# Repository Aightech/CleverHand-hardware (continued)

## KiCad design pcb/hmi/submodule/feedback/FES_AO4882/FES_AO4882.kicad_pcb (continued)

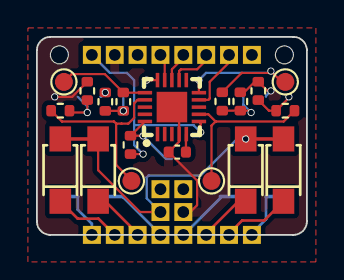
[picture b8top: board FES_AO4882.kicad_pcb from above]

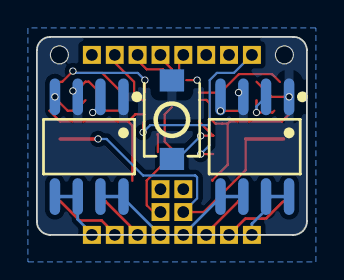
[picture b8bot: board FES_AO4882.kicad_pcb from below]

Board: 4 copper layers, 15.0 x 11.0 mm, 42 parts (3 on the bottom side), 26 nets.

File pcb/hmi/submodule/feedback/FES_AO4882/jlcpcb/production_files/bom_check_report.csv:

Status,RefDes,Qty,LCSC,BOM_Comment,LCSC_Package,LCSC_Describe,Matched,Issues,FallbackNote
OK,R2,1,C25744,10K,0402,-55℃~+155℃ 10kΩ 50V 62.5mW Thick Film Resistor ±1% ±100ppm/℃ 0402 Chip Resistor - Surface Mount ROHS,describe~substring,,
OK,"R1,R3,R6,R7",4,C11702,1k,0402,-55℃~+155℃ 1kΩ 50V 62.5mW Thick Film Resistor ±1% ±100ppm/℃ 0402 Chip Resistor - Surface Mount ROHS,describe~substring,,
OK,"R4,R5,R8,R9",4,C4109,2k,0402,-55℃~+155℃ 2kΩ 50V 62.5mW Thick Film Resistor ±1% ±100ppm/℃ 0402 Chip Resistor - Surface Mount ROHS,describe~substring,,
OK,C1,1,C23733,4.7uF,0402,10V 4.7uF X5R ±20% 0402 Multilayer Ceramic Capacitors MLCC - SMD/SMT ROHS,capacitance,,
FAIL,"Q1,Q2",2,C3040598,AO4882_C3040598,,-50℃~+150℃ 1.45nF 140pF 2 N-Channel 2.5V@250uA 21.6nC@10V 220pF@25V 25mΩ@4.5V 2W 40V 8A SOP-8 MOSFETs ROHS,,no clear feature match for generic part,
OK,"U1,U2,U3,U5",4,C5120757,DS12W-MS,,-65℃~+125℃ 1A 20V 500uA@20V 550mV@1A Independent SOD-123FL Diodes - General Purpose ROHS,model/brand,,
OK,U4,1,C493490,HC32L110C6UA-SFN20TR,,1.8V~5.5V 12bit 16 32KB 32MHz ARM Cortex-M0 FLASH WQFN-20-EP(3x3) Microcontrollers (MCU/MPU/SOC) ROHS,model/brand,,
OK,SW1,1,C455280,TS-1088R-02026,,"100,000 Cycles 12V 2.6N 2.93mm 2mm 3.9mm 50mA Black Round Button SMD(SMT) Tab SPST Surface Mount,Vertical Without Bracket SMD,4x3mm Tactile Switches ROHS",model/brand,,

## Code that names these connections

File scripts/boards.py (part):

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# ============ COM_MOD_PAK ============
def com_mod_pak():
    s=Sheet("COM_MOD_PAK","COM_MOD_PAK - v3 communication module B (HC32L110 + SLG46826)")
    s.text("HC32L110C6UA QFN-20 (CSP-16 rejected: inner balls not routable with JLC rules). v2 pinout kept: SDA P35, SCL P36, STOP_IN P31 (=SWCLK), STOP_OUT P02, LED P01. Freed ADD pins: P34/P33 = private I2C to the GreenPAK, P03/P15/P14/P32 = AUX4..7 (node-local), P23 user button.",20,20,1.8)
    s.part("U","00_lcsc","HC32L110C6UA-SFN20TR",90,100,{
        "1":"RESETB","2":"LED_DI","3":g("STOP_OUT"),"4":G,"5":"VCAP","6":P3,"7":g("AUX4"),"8":g("AUX5"),"9":g("AUX6"),"10":"BTN",
        "11":"NC","12":"NC","13":"NC","14":"SWDIO","15":g("STOP_IN"),"16":g("AUX7"),"17":"PAK_SDA","18":"PAK_SCL","19":g("SDA"),"20":g("SCL"),"21":G},lcsc=LC["HC32"])
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# ============ BUS_FPC ============
def bus_fpc():
    s=Sheet("BUS_FPC","BUS_FPC - passive bus board, two 18-way FPC (v2 cable pinout)")
    s.text("IN connector: pin k = v2 cable pin k. OUT connector is pin-reversed (pin k = cable pin 19-k). STOP: IN -> STOP_IN, OUT <- STOP_OUT.",20,20,1.8)
    nin=dict(CABLE); nin["13"]=g("STOP_IN")
    s.part("J","00_lcsc","FPC-05F-18PH20",60,110,nin,lcsc=LC["FPC"],value="FPC IN")
    nout={}
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    nid={str(k):CABLE[str(k)] for k in range(1,19) if k!=13}; nid["13"]="NC"
    s.part("J","Connector_Generic","Conn_02x09_Odd_Even",70,110,nid,value="IDC 2x9 1.27",footprint="Connector_PinHeader_1.27mm:PinHeader_2x09_P1.27mm_Vertical_SMD")
    s.part("J","00_lcsc","SM02B-SRSS-TB(LF)(SN)",150,110,{"1":g("STOP_IN"),"2":g("STOP_OUT"),"3":G,"4":G},lcsc=LC["SH"],value="STOP link")
    s.text("STOP link: pin1 = STOP_IN (from previous node), pin2 = STOP_OUT (to next node); crossed 2-wire cable",120,125,1.3)
    stack_field(s,250,110,"bus","3x10 stack field: rows A+B and AUX0..3 connected, row C local lines left open")
    tp(s,60,180,"VIN_TP")
    s.passive("C","100nF",140,180,P3,G)
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    usb_block(s,60,210)
    battery_block(s,200,210,"MIC")
    dac_block(s,60,270)
    stack_field(s,330,90,"ctrl","3x10 stack field, CTRL: drives row B (STOP_IN unused), SDA_L/SCL_L strapped to SDA/SCL, VIN = battery, AUX0..3 on ADC pins, AUX4..7 on GPIO")
    s.flag("VBUS",20,250); s.flag("+BATT",30,250); s.flag("GND",40,250); s.flag("+3.3V",50,250)
    return s
# ============ CTRL_ESP32S3 ============
def ctrl_esp():
    s=Sheet("CTRL_ESP32S3","CTRL_ESP32S3 - ESP32-S3FH4R2 controller node (chip-down)")
    s.text("ESP32-S3FH4R2 chip-down: 40 MHz crystal, TDK chip antenna with pi-match (values TBD at tuning), native USB on GPIO19/20. Mono node or chain head; SDA_L/SCL_L strapped.",20,20,1.8)
    s.part("U","00_lcsc","ESP32-S3FH4R2",80,110,{
        "2":P3,"3":P3,"20":P3,"46":P3,"55":P3,"56":P3,"29":P3,"57":G,"4":"CHIP_PU","5":"GPIO0","1":"LNA_IN","53":"XTAL_N","54":"XTAL_P","25":"D-","26":"D+","49":"U0TXD","50":"U0RXD",
        "17":g("SCLK"),"16":g("PICO"),"18":g("POCI"),"15":g("CSB"),"14":g("AUX7"),"9":g("A0"),"10":g("A1"),"11":g("A2"),"12":g("A3"),"13":g("A4"),"19":g("STOP_OUT"),
        "6":g("SDA"),"7":g("SCL"),"8":g("AUX4"),"23":g("AUX7"),"24":g("AUX5"),"27":g("AUX6"),"43":"LED_DI","38":"BTN","39":g("AUX0"),"40":g("AUX1"),"41":g("AUX2"),"42":g("CLK"),"44":"CHG_STAT","45":g("AUX3"),
        "21":"NC","22":"NC","28":"NC","30":"NC","31":"NC","32":"NC","33":"NC","34":"NC","35":"NC","36":"NC","37":"NC","47":"NC","48":"NC","51":"NC","52":"NC"},lcsc=LC["ESP"])
    s.passive("C","10uF",150,60,P3,G,size="0402"); s.passive("C","100nF",160,60,P3,G); s.passive("C","100nF",170,60,P3,G); s.passive("C","100nF",180,60,P3,G); s.passive("C","1uF",190,60,P3,G)
    s.text("CHIP_PU: 10k pull-up + 1uF (RC reset), reset button. GPIO0: 10k pull-up + boot button.",150,80,1.3)
    s.passive("R","10k",150,95,P3,"CHIP_PU"); s.passive("C","1uF",160,95,"CHIP_PU",G); button(s,175,95,"CHIP_PU",False)
    s.passive("R","10k",150,125,P3,"GPIO0"); button(s,175,125,"GPIO0",False); button(s,215,125,"BTN")
    s.part("Y","00_lcsc","40MHZ_3225_12PF_10PPM",150,160,{"1":"XTAL_P","3":"XTAL_N","2":G,"4":G},lcsc=LC["XTAL"],value="40MHz 12pF")
    s.passive("C","12pF",170,160,"XTAL_P",G); s.passive("C","12pF",180,160,"XTAL_N",G)
    s.text("RF: LNA_IN -> C -> L -> ANT with shunt C (pi-match, values TBD)",150,185,1.3)
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    usb_block(s,60,260)
    battery_block(s,200,260,"AP")
    dac_block(s,60,320)
    stack_field(s,330,90,"ctrl","3x10 stack field, CTRL: drives row B (STOP_IN unused), SDA_L/SCL_L strapped to SDA/SCL, VIN = battery, AUX0..3 / AUX4..7 on GPIO")
    s.flag("VBUS",20,250); s.flag("+BATT",30,250); s.flag("GND",40,250); s.flag("+3.3V",50,250)
    return s
# ============ VIB_DRV2625 ============
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    s.part("U","00_lcsc","DRV2625YFFR",80,90,{"C2":P3,"B3":G,"A2":"REG","C3":"OUT-","A3":"OUT+","B1":g("SDA_L"),"C1":g("SCL_L"),"A1":g("AUX7"),"B2":g("AUX6")},lcsc=LC["DRV"])
    s.passive("C","1uF",130,80,"REG",G); s.passive("C","1uF",140,80,P3,G); s.passive("C","10uF",150,80,P3,G,size="0402")
    s.part("J","00_lcsc","SM02B-SRSS-TB(LF)(SN)",80,140,{"1":"OUT+","2":"OUT-","3":G,"4":G},lcsc=LC["SH"],value="MOTOR")
    stack_field(s,250,110,{"GND":G,"3V3":P3,"SDA_L":g("SDA_L"),"SCL_L":g("SCL_L"),"AUX6":g("AUX6"),"AUX7":g("AUX7")},"3x10 stack field, H-i2c: populate row A power pins, C1/C2 (local I2C), C7/C8 (AUX6/AUX7); other positions unpopulated")
    s.flag("+3.3V",20,200); s.flag("GND",30,200)
    return s

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
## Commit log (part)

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2021-08-24 v7-panel
    smd0201
2021-08-24 panelized
2021-08-29 jst sh conn
2021-08-29 dim changed to be panalized 3x4
2021-08-30 add rdy and sync
2021-09-24 placement
2021-09-24 gnd-vdd common
2021-09-24 finished
2021-09-24 pics
2021-09-25 panelization
2021-09-25 component val + minor debug
2021-09-26 Create clvHd.s##
2021-09-26 3d rendering
2021-09-26 update colors + text
2021-09-27 correction led
2021-09-27 redesign
2021-10-28 Xtal fixed + logo
2021-10-29 animation
2021-11-08 added master FES EMG folders
2021-11-26 almost fully routed
2021-11-27 ready for prod
2021-11-30 master update
2021-11-30 refactor git
2021-12-14 shrinken
2021-12-16 dir indication + lvl3 gnd plane
2022-01-23 double gate nand
2022-01-27 socket design
2022-02-06 long board
2022-04-12 global setup
2022-04-12 partial routing
2022-04-12 almost completely routed
2022-04-12 fully routed + text
2022-04-12 bottom stop correction + bottom text
2022-06-26 visual mod
2022-07-01 nand new package
    changed the json package for a vssop package to make is easier to solder. updated README, docs and CAM
2022-07-02 panelization + datasheet
2022-07-06 added stl model
2022-07-06 license and co
2022-07-06 added some pics
2022-07-15 neopixel
2022-07-16 fixed position c4-r1
2022-07-31 fixed g00 pinout
2022-10-26 v3.0 on kicad
2022-10-28 finished v3
2022-10-31 fixed some panel bug for jlcpcb
2022-11-01 v3.1 fixed solder and paste mask and some via pos
2022-12-30 cleanup directory
2023-02-22 new module with hc32l110 and some extension board
2023-05-29 lot of modification, preparing a refactor + some rendering
2023-09-08 updated bridge
2023-09-13 updated bridge board
2023-09-14 cleanup
2023-11-15 new version logicGate+hc32l to mitigate CS speed while keeping new features
2023-11-28 new modules EMGDAQ and COMMOD
2023-11-30 reshaped the modules boards sizes
2023-11-30 blender module assembly
2023-12-05 some cleaning + edge plating dry electrode
2023-12-05 some rendring
2023-12-07 finished rooting emgdaq + schematic commod
2023-12-30 lot of updates on ads93,flex,commod,pad
2024-01-02 finished ads93,commod,drypad,flexpad,jackconn,imubno + plot and render
2024-03-29 INA331 IMUICM
2024-03-29 jack, dry electrode
2024-03-30 refactor and fixing most of the modules
2024-03-30 new dry flex
2024-03-30 cleaned all modules + production files
2024-03-31 lot of rendering and documentaion
2024-04-01 fixed INA331 wrong package and add ext ref
2024-04-01 regenerated production files for INA331
2024-04-01 cleaned kicad folder
2024-04-01 renamed stl files
2024-04-17 renamed SPI buses
2024-06-24 fixed COM_MOD grounding issues
2024-07-02 Rename pinout2.png to initialisation/pinout2.png
2024-07-18 added progress state of the submodules
2024-07-28 minor update: added pins to access i2c pins of the com bus
2024-07-28 major update: fixed inversion of i2c lines + added pull up resistors + rotated 180deg fpc conector
2024-07-29 fixed ref number of FPC connectors and added ref numbers of resitors
2024-08-17 modified pins to expose in6 and gnd for potential filtering
2024-08-17 increase size of the board to make it easier to screw
2024-08-17 new dry electectrodes for ads1295 module
2024-08-17 pannel for new dry electrodes
2024-08-25 v3.2 fixed issue between GND and GNDA
2024-08-26 update production files of shield controller teensy
2024-09-02 mono controller, to have module working on their own and comunicate via wifi
2024-09-02 finished mono moudule, should be ready for manufacture
2024-09-02 fixed pico controller shield to match v3 modules
2024-09-02 minor fix on teensy shield
2024-09-03 fixed MONOCOM ERC and DRC: via size, missing pins
2024-09-04 generated production files and plots of controllers shield and mono ctrl
2024-10-08 added 2x2 panels for COM_MOD and EMD_ADS1293
2024-10-12 fixed castelated holes for beter fixation on interface board
2024-10-12 added mid size to fit better with ads1293 module and standad xtal + some modificaion
2024-10-12 minor graphical changes
2024-10-12 added some docs
2024-10-12 added doc and regenerated gerbers
2025-03-25 added esp32c3xiaoshield
2025-03-25 some work on mono controller
2026-01-04 refactoring and redocumenting all modules
2026-01-12 fixed readme
